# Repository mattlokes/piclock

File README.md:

WordClock
=======

RGB Colour Word Clock, Powered by a Raspberry Pi/Similar Embedded Linux Board with matrix display capabilities.

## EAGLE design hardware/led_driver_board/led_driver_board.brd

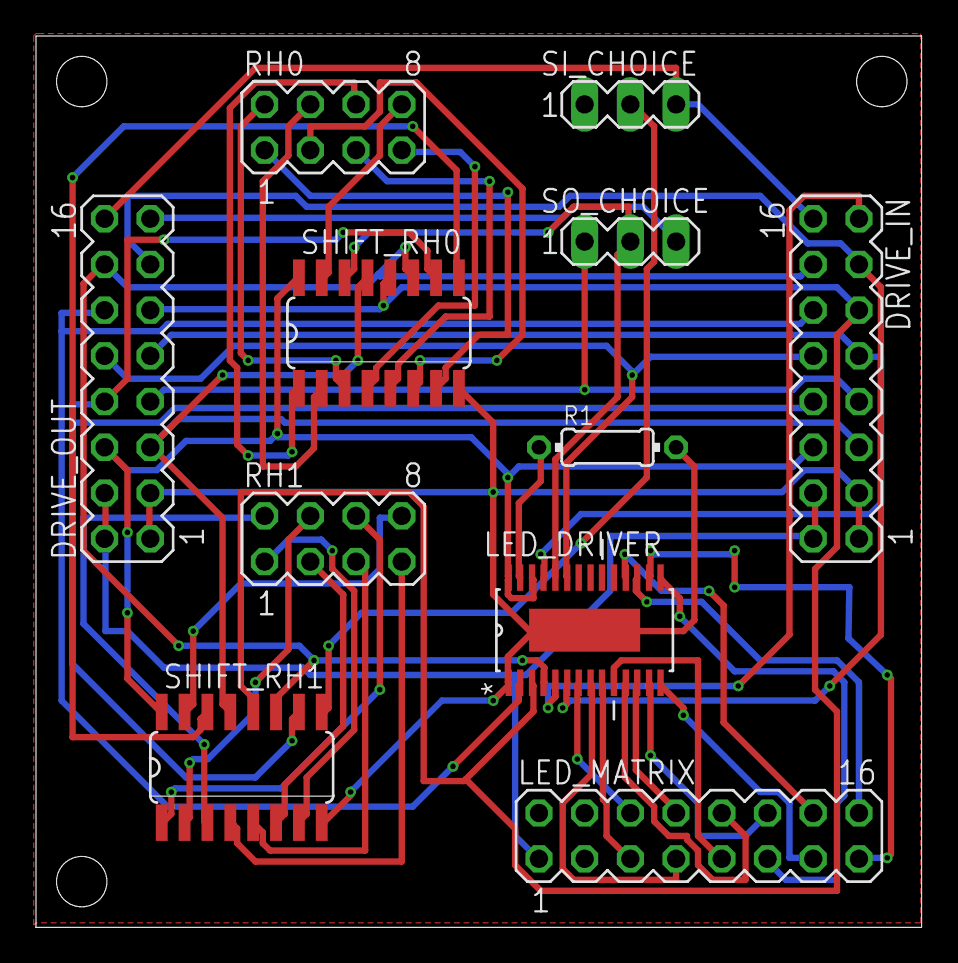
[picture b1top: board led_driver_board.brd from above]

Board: 2 copper layers, 49.2 x 49.5 mm, 11 parts (0 on the bottom side), 47 nets.

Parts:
DRIVE_IN: MA08-2
DRIVE_OUT: MA08-2
LED_DRIVER: TLC59401PWP; SOP65P640X120-29N
LED_MATRIX: MA08-2
R1: 0204/7
RH0, RH1: MA04-2
SHIFT_RH0, SHIFT_RH1: 74HC595D; SO16
SI_CHOICE: MA03-1
SO_CHOICE: MA03-1

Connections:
B1: LED_DRIVER.16, LED_MATRIX.15
B2: LED_DRIVER.13, LED_MATRIX.12
B3: LED_DRIVER.10, LED_MATRIX.9
B4: LED_DRIVER.7, LED_MATRIX.6
BL: DRIVE_IN.12, DRIVE_OUT.12, LED_DRIVER.2
ER: DRIVE_IN.10, DRIVE_OUT.10, LED_DRIVER.23
G1: LED_DRIVER.17, LED_MATRIX.16
G2: LED_DRIVER.14, LED_MATRIX.13
G3: LED_DRIVER.11, LED_MATRIX.10
G4: LED_DRIVER.8, LED_MATRIX.7
GND: DRIVE_IN.1, DRIVE_IN.3, DRIVE_OUT.1, DRIVE_OUT.3, LED_DRIVER.1, LED_DRIVER.29, R1.2, SHIFT_RH0.8, SHIFT_RH1.8
LSO: LED_DRIVER.24, SHIFT_RH0.14, SO_CHOICE.2
unnamed: LED_DRIVER.27, R1.1
unnamed: SHIFT_RH0.9, SHIFT_RH1.14
OE: DRIVE_IN.5, DRIVE_OUT.5, SHIFT_RH0.13, SHIFT_RH1.13
PC: DRIVE_IN.9, DRIVE_OUT.9, LED_DRIVER.25
PV: DRIVE_IN.2, DRIVE_IN.4, DRIVE_OUT.2, DRIVE_OUT.4, LED_MATRIX.1
R1: LED_DRIVER.18, LED_MATRIX.14
R2: LED_DRIVER.15, LED_MATRIX.11
R3: LED_DRIVER.12, LED_MATRIX.8
R4: LED_DRIVER.9, LED_MATRIX.5
RE: DRIVE_IN.8, DRIVE_OUT.8, SHIFT_RH0.10, SHIFT_RH1.10
ROW0: RH0.8, SHIFT_RH0.15
ROW1: RH0.6, SHIFT_RH0.1
ROW2: RH0.4, SHIFT_RH0.2
ROW3: RH0.2, SHIFT_RH0.3
ROW4: RH0.7, SHIFT_RH0.4
ROW5: RH0.5, SHIFT_RH0.5
ROW6: RH0.3, SHIFT_RH0.6
ROW7: RH0.1, SHIFT_RH0.7
ROW8: RH1.8, SHIFT_RH1.15
ROW9: RH1.6, SHIFT_RH1.1
ROW10: RH1.4, SHIFT_RH1.2
ROW11: RH1.2, SHIFT_RH1.3
ROW12: RH1.7, SHIFT_RH1.4
ROW13: RH1.5, SHIFT_RH1.5
ROW14: RH1.3, SHIFT_RH1.6
ROW15: RH1.1, SHIFT_RH1.7
RR: DRIVE_IN.7, DRIVE_OUT.7, SO_CHOICE.1
RSO: SHIFT_RH1.9, SI_CHOICE.2
SCK: DRIVE_IN.14, DRIVE_OUT.14, LED_DRIVER.4, SHIFT_RH0.11, SHIFT_RH1.11
SI: DRIVE_IN.16, DRIVE_OUT.16, SI_CHOICE.3
SO: DRIVE_IN.15, LED_DRIVER.5
SO_L: DRIVE_OUT.15, SO_CHOICE.3
VCC: DRIVE_IN.6, DRIVE_OUT.6, LED_DRIVER.26, LED_DRIVER.28, SHIFT_RH0.16, SHIFT_RH1.16
VP: DRIVE_IN.13, DRIVE_OUT.13, LED_DRIVER.6
XL: DRIVE_IN.11, DRIVE_OUT.11, LED_DRIVER.3, SHIFT_RH0.12, SHIFT_RH1.12

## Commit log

2013-04-05 Setting Up Repo
2013-04-05 tidying up
2013-04-05 Created virtual grid, which reads in config from grid.conf then generates a piclock simulation
2013-04-05 Add initial documentation to repo
2013-04-06 Create sim scripts and Create GridInterface_Sim file structure
2013-04-07 Seperate Threaded GUI Window with command queue interface, basic clear and set pixel functions implemented, basic test working
2013-04-07 Seperate Threaded GUI Window with command queue interface, basic clear and set pixel functions implemented, basic test working2
2013-04-07 Add GridWordDef.py , which contains pixel mappings to words need for time
2013-04-07 Add function placeholder for printing the time
2013-04-07 Fully working wordclock functionality with simulator, needs commenting and tidying up, but seems to work
2013-04-07 Bugfix for the time at "o\'clock\'
2013-04-07 Bugfix for minutes being less that 10
2013-04-07 Bugfix for quarter past the hour
2013-04-07 rearranged grid to make eighteen look better, and added the time of the time function in.
2013-05-27 Added STM32 Code Make Files and Libraries. Minigrid added.
2013-05-27 Add Drill Template SVG
2013-05-28 Got Indiviual LED Control, Current code dims one row of LEDs
2014-07-16 Adding pic32 code for full system
2014-07-16 Removing Old STM code used for very first prototype
2014-07-16 Add LED Driver board PCB Eagle files and Gerbers
2014-07-16 Added 3D Printed Parts SCAD and STL files, As well as Kicad Ledmatrix designs with Gerbers
2014-11-28 Add Python Scripts for communicating with the PIC32
2014-11-28 Add Hex Snapshots of working Code
2014-11-29 Rename directory
2014-11-29 Start Creating Python Framework, add clockApp
2014-11-29 Add hwInterface to render frames on the LED Grid
2014-11-30 Add Component Glue Function main.py
2014-11-30 Fix mins to Bug, Cleanup Exit code, fix syntax bugs. Working
2014-11-30 Add Websocket Control Module
2014-11-30 Update Clock Application to decode commands
2014-11-30 Add Initial Pages to send Commands
2014-11-30 add WebSocket Interface to system
2014-12-04 Update of all PIC32 Code, current works using DMA to read UART Data
2014-12-04 Tidy PIC32 Code up
2014-12-04 Add fastRx mode to hwInterface to allow lower cpu usage and faster uart rx
2014-12-05 Cleanup webpages and improve cpu usage
2014-12-10 Join Cmd and Frame Queues and use Get properly to save CPU usage
2014-12-10 Fix Minor Bugs
2014-12-10 Add fakeSerial switch to allow simulations of the clock without plugging it in
2014-12-11 Add Digital Clock Mode for ClockApp
2014-12-12 Add Mega Clock Mode
2014-12-12 rework system directory structure and covert frameLib to a proper static class
2014-12-12 more system rework
2014-12-12 Move clockAppConsts toa seperate file
2014-12-12 Move Consts out of Clock App into seperate file
2014-12-12 Add Git Ignore File
2014-12-13 Move webserver content around
2014-12-13 Move More webserver content around, create webserver python wrapper, create colourTestApp
2014-12-13 Add CreateColourFrame function frameLibrary, and edit webserver config
2014-12-13 Split lighttpd config file into PC and PI versions
2014-12-13 Fixing ser instantiation to be self.ser.
2014-12-13 add webserver temp directory to the ignore file
2014-12-13 add Vertical Line Animation
2014-12-14 Make Vertical Line Animation More interesting and faster
2014-12-21 Add Colour Translation Table
2014-12-24 Create Module Instantiation Loop & Message Routing Prototype
2014-12-24 Lower CPU Usage and small changes
2014-12-27 Tidy Up Webpage Libraries
2014-12-27 Update Webpage Structure and python webserver module
2014-12-27 add more ignores to .gitignore
2014-12-27 Add Basic Colour NonLinearity correction
2014-12-27 Changes due to repo rename and main tidy up
2014-12-28 Fix Kill behaviour, to close down safetly, Add system print class to print nicely formatted messages, Add rxQueue to wsInterface and tidy various bits up
2014-12-28 Add Status Page Template, Fix ClockApp Wepbage as well as tidying up navigation menu.
2014-12-28 Update ClockApp and Webpage to add controls and handling, Fix One Minute Bug
2014-12-29 Add Pause and Resume to Applications
2014-12-29 NEW APPLICATION HANDLING, use applciation object to help with code resuse
2014-12-29 Add ColourTestApp Page and add application switching mechanism
2014-12-31 Pi Fixes
2015-01-02 Add Get Pixel Value Function to frameLib
2015-01-02 Add Snake Application
2015-01-02 Fix Snake App Html Page
2015-07-23 Fix Html Pages to use server IP for websocket rather than fixed
2015-07-26 Fix SnakeApp Button Style
2015-07-26 Initial Changes to get WS2812b LED interface working on PIC32
2015-07-26 Add WS2812b LED PCBS
2015-08-02 Attempted Fix for SFP Error (Suspected None Atomic access between threads)
2015-08-02 Snake Control Fix
2015-08-03 Add Clock Transitions
2015-08-04 Add platform argument to allow webserver to run on diffrent platform configs
2015-08-04 Add Shift Frame Functions in frameLib, and clean up Clock Transitions
2015-08-04 Implemented VSlide Clock Transition
2015-08-10 Support for WS2812B matrix only
2015-09-05 Structure overhaul, abandon dodgy Python threading and use ZeroMQ for communications between interfaces and applications
2015-09-05 Further Restructure, all Applications and interfaces updated
2015-09-07 Finish ZeroMQ rework, System working, still need to right C hardware interface
2015-09-08 Add Python Hardware Component
2015-09-24 Update to latest everything
2015-09-24 Add New direct Raspberry Pi WS2812 driving C code
2015-09-24 Direct LED Raspberry Pi interface working, need to fix colours though
2015-09-24 Fix all the Colour Ordering between the LED interface adn the python modules
2015-09-29 updated temporary run script
2015-09-29 clockapp: Add Horizontal Slide Transition and framework for other transitions
2015-10-01 Add Fade Clock Transition
2015-10-03 Flip Clock 180 degrees as its now *upside down*
2015-10-05 Repo Cleanup
2015-12-15 Bring Repo upto Date with Clock
2015-12-15 Add ws2812b ledInterface Binary
2015-12-16 Updated Install scripts to contain all dependancies
2015-12-18 Create Notifiers Placeholder
2016-03-03 Raspbian Jessie Support, ZMQ fixes and install script
2016-03-04 Systemd Service Support; Rework webserver and ledDisplay startup; Rework lighttpd config file; Implement Install script
2016-03-05 Repo Tidy Up
2016-03-11 Overhaul Clock Control Page, to use JQUERY events rather than ineffecient timer method
2016-03-11 Further ClockApp Webpage Cleanup
2016-03-11 Add Keyboard Controls to Snake
2016-03-11 Fix FrameLib Colour Definition
2016-03-12 Add Websocket msg tx from Server to Client, Return Application state to the client to keep interface in sync with internal state
2016-09-18 Updates to install script
2017-08-26 Add new webDisplay that simulates clock face in the browser, also tidy up displays directory, each display has own directory.
